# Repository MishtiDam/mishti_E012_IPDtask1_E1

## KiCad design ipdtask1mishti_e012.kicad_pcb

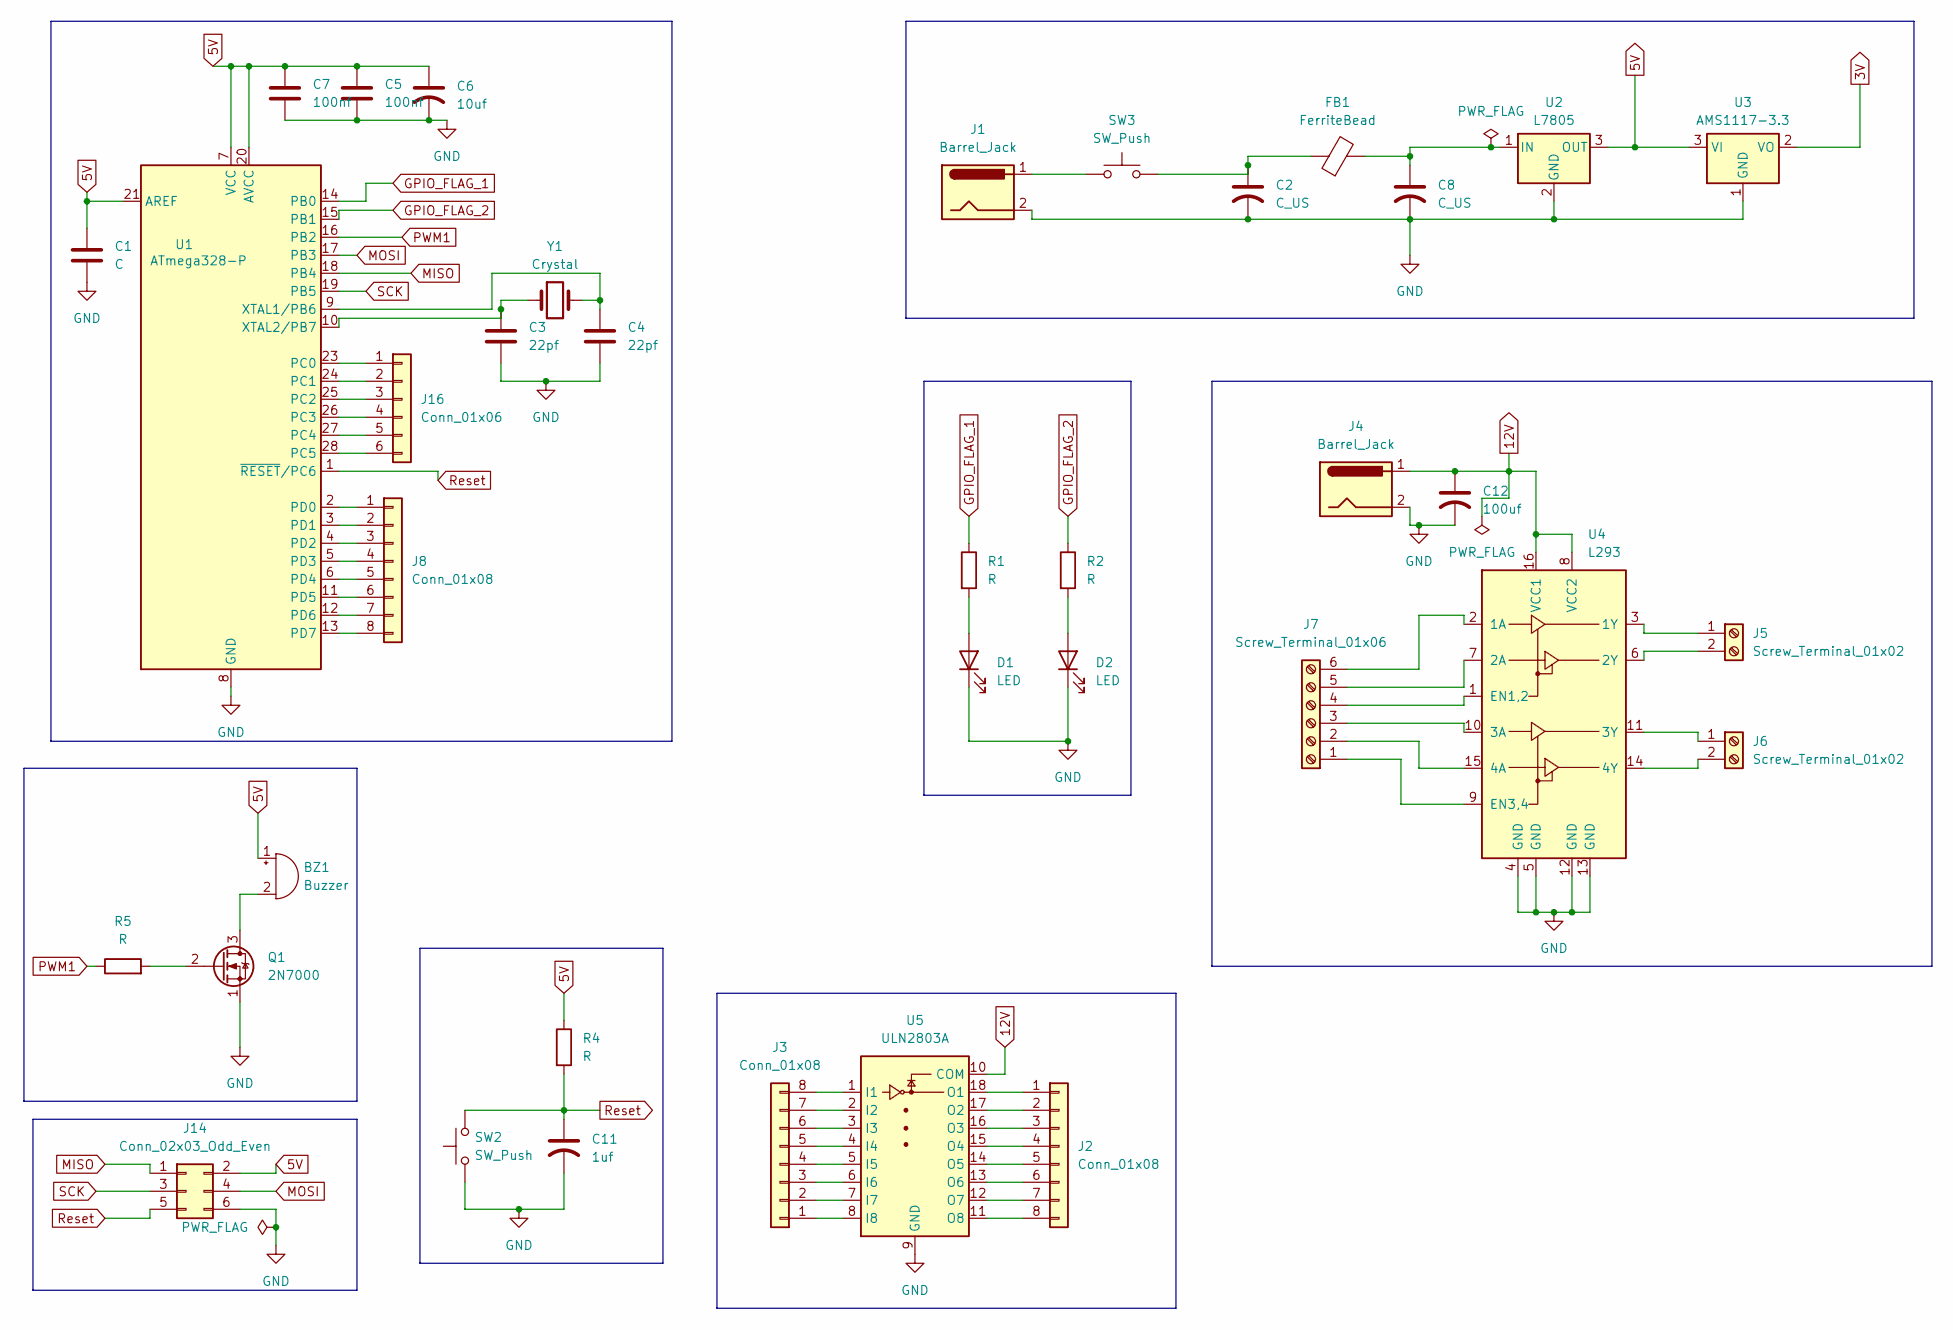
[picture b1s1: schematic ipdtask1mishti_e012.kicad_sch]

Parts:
BZ1: Buzzer; Buzzer_12x9.5RM7.6
C1: C; CP_Radial_D7.5mm_P2.50mm
C2, C8: C_US; CP_Radial_D4.0mm_P1.50mm
C3, C4: 22pf; CP_Radial_D7.5mm_P2.50mm
C5, C7: 100nf; CP_Radial_D7.5mm_P2.50mm
C6: 10uf; CP_Radial_D7.5mm_P2.50mm
C11: 1uf; CP_Radial_D7.5mm_P2.50mm
C12: 100uf; CP_Radial_D7.5mm_P2.50mm
D1, D2: LED; LED_D8.0mm
FB1: FerriteBead; LairdTech_28C0236-0JW-10
J1, J4: Barrel_Jack; BarrelJack_CUI_PJ-063AH_Horizontal
J2, J3, J8: Conn_01x08; PhoenixContact_GMSTBV_2,5_8-GF-7,62_1x08_P7.62mm_Vertical_T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
J5, J6: Screw_Terminal_01x02; PhoenixContact_GMSTBV_2,5_2-GF-7,62_1x02_P7.62mm_Vertical_T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
J7: Screw_Terminal_01x06; PhoenixContact_GMSTBV_2,5_6-GF-7,62_1x06_P7.62mm_Vertical_T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
J14: Conn_02x03_Odd_Even; IDC-Header_2x03_P2.54mm_Vertical
J16: Conn_01x06; PhoenixContact_GMSTBV_2,5_6-GF-7,62_1x06_P7.62mm_Vertical_T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
Q1: 2N7000; TO-92_Inline
R1, R2, R4, R5: R; R_Axial_DIN0207_L6.3mm_D2.5mm_P7.62mm_Horizontal
SW2, SW3: SW_Push; SW_PUSH_6mm
U1: ATmega328-P; DIP-28_W7.62mm
U2: L7805; TO-220-3_Vertical
U3: AMS1117-3.3; SOT-223-3_TabPin2
U4: L293; DIP-16_W7.62mm
U5: ULN2803A; DIP-18_W7.62mm
Y1: Crystal; Crystal_C26-LF_D2.1mm_L6.5mm_Vertical

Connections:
3V: U3.2 (VO)
5V: BZ1.1 (+), C1.1, C5.1, C6.1, C7.1, J14.2, R4.1, U1.7 (VCC), U1.20 (AVCC), U1.21 (AREF), U2.3 (OUT), U3.3 (VI)
12V: C12.1, J4.1, U4.8 (VCC2), U4.16 (VCC1), U5.10 (COM)
GND: C1.2, C2.2, C3.2, C4.2, C5.2, C6.2, C7.2, C8.2, C11.2, C12.2, D1.1 (K), D2.1 (K), J1.2, J4.2, J14.6, Q1.1 (S), SW2.1, U1.8 (GND), U1.22 (GND), U2.2 (GND), U3.1 (GND), U4.4 (GND), U4.5 (GND), U4.12 (GND), U4.13 (GND), U5.9 (GND)
GPIO_FLAG_1: R1.1, U1.14 (PB0)
GPIO_FLAG_2: R2.1, U1.15 (PB1)
MISO: J14.1, U1.18 (PB4)
MOSI: J14.4, U1.17 (PB3)
unnamed: BZ1.2 (-), Q1.3 (D)
unnamed: C2.1, FB1.1, SW3.2
unnamed: D1.2 (A), R1.2
unnamed: D2.2 (A), R2.2
unnamed: J1.1, SW3.1
unnamed: J2.1, U5.18 (O1)
unnamed: J2.2, U5.17 (O2)
unnamed: J2.3, U5.16 (O3)
unnamed: J2.4, U5.15 (O4)
unnamed: J2.5, U5.14 (O5)
unnamed: J2.6, U5.13 (O6)
unnamed: J2.7, U5.12 (O7)
unnamed: J2.8, U5.11 (O8)
unnamed: J3.1, U5.8 (I8)
unnamed: J3.2, U5.7 (I7)
unnamed: J3.3, U5.6 (I6)
unnamed: J3.4, U5.5 (I5)
unnamed: J3.5, U5.4 (I4)
unnamed: J3.6, U5.3 (I3)
unnamed: J3.7, U5.2 (I2)
unnamed: J3.8, U5.1 (I1)
unnamed: J5.1, U4.3 (1Y)
unnamed: J5.2, U4.6 (2Y)
unnamed: J6.1, U4.11 (3Y)
unnamed: J6.2, U4.14 (4Y)
unnamed: J7.1, U4.9 (EN3,4)
unnamed: J7.2, U4.15 (4A)
unnamed: J7.3, U4.10 (3A)
unnamed: J7.4, U4.1 (EN1,2)
unnamed: J7.5, U4.7 (2A)
unnamed: J7.6, U4.2 (1A)
unnamed: J8.1, U1.2 (PD0)
unnamed: J8.2, U1.3 (PD1)
unnamed: J8.3, U1.4 (PD2)
unnamed: J8.4, U1.5 (PD3)
unnamed: J8.5, U1.6 (PD4)
unnamed: J8.6, U1.11 (PD5)
unnamed: J8.7, U1.12 (PD6)
unnamed: J8.8, U1.13 (PD7)
unnamed: J16.1, U1.23 (PC0)
unnamed: J16.2, U1.24 (PC1)
unnamed: J16.3, U1.25 (PC2)
unnamed: J16.4, U1.26 (PC3)
unnamed: J16.5, U1.27 (PC4)
unnamed: J16.6, U1.28 (PC5)
unnamed: Q1.2 (G), R5.2
unnamed: C4.1, U1.9 (XTAL1/PB6), Y1.2
unnamed: C3.1, U1.10 (XTAL2/PB7), Y1.1
unnamed: C8.1, FB1.2, U2.1 (IN)
PWM1: R5.1, U1.16 (PB2)
Reset: C11.1, J14.5, R4.2, SW2.2, U1.1 (~RESET/PC6)
SCK: J14.3, U1.19 (PB5)

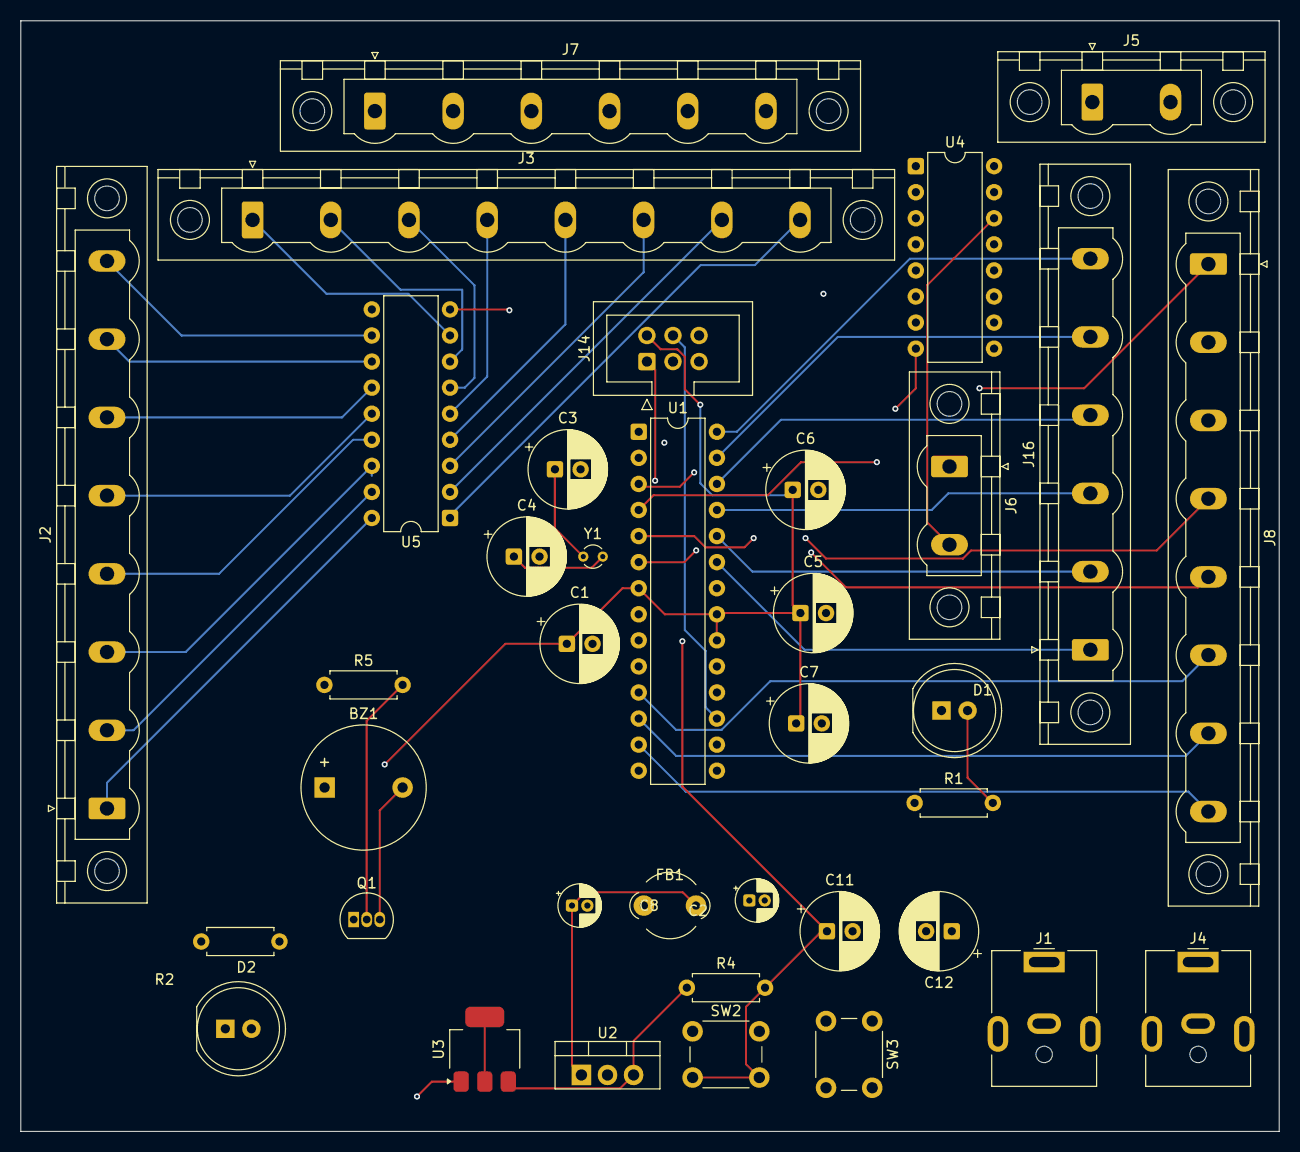
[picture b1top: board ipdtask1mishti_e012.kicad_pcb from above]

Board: 4 copper layers, 122.6 x 108.2 mm, 37 parts (0 on the bottom side), 59 nets.
